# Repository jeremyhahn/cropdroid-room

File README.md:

# cropdroid-room

## Support

Please consider supporting this project for ongoing success and sustainability. I'm a passionate open source contributor making a professional living creating free, secure, scalable, robust, enterprise grade, distributed systems and cloud native solutions.

I'm also available for international consulting opportunities. Please let me know how I can assist you or your organization in achieving your desired security posture and technology goals.

https://github.com/sponsors/jeremyhahn

https://www.linkedin.com/in/jeremyhahn

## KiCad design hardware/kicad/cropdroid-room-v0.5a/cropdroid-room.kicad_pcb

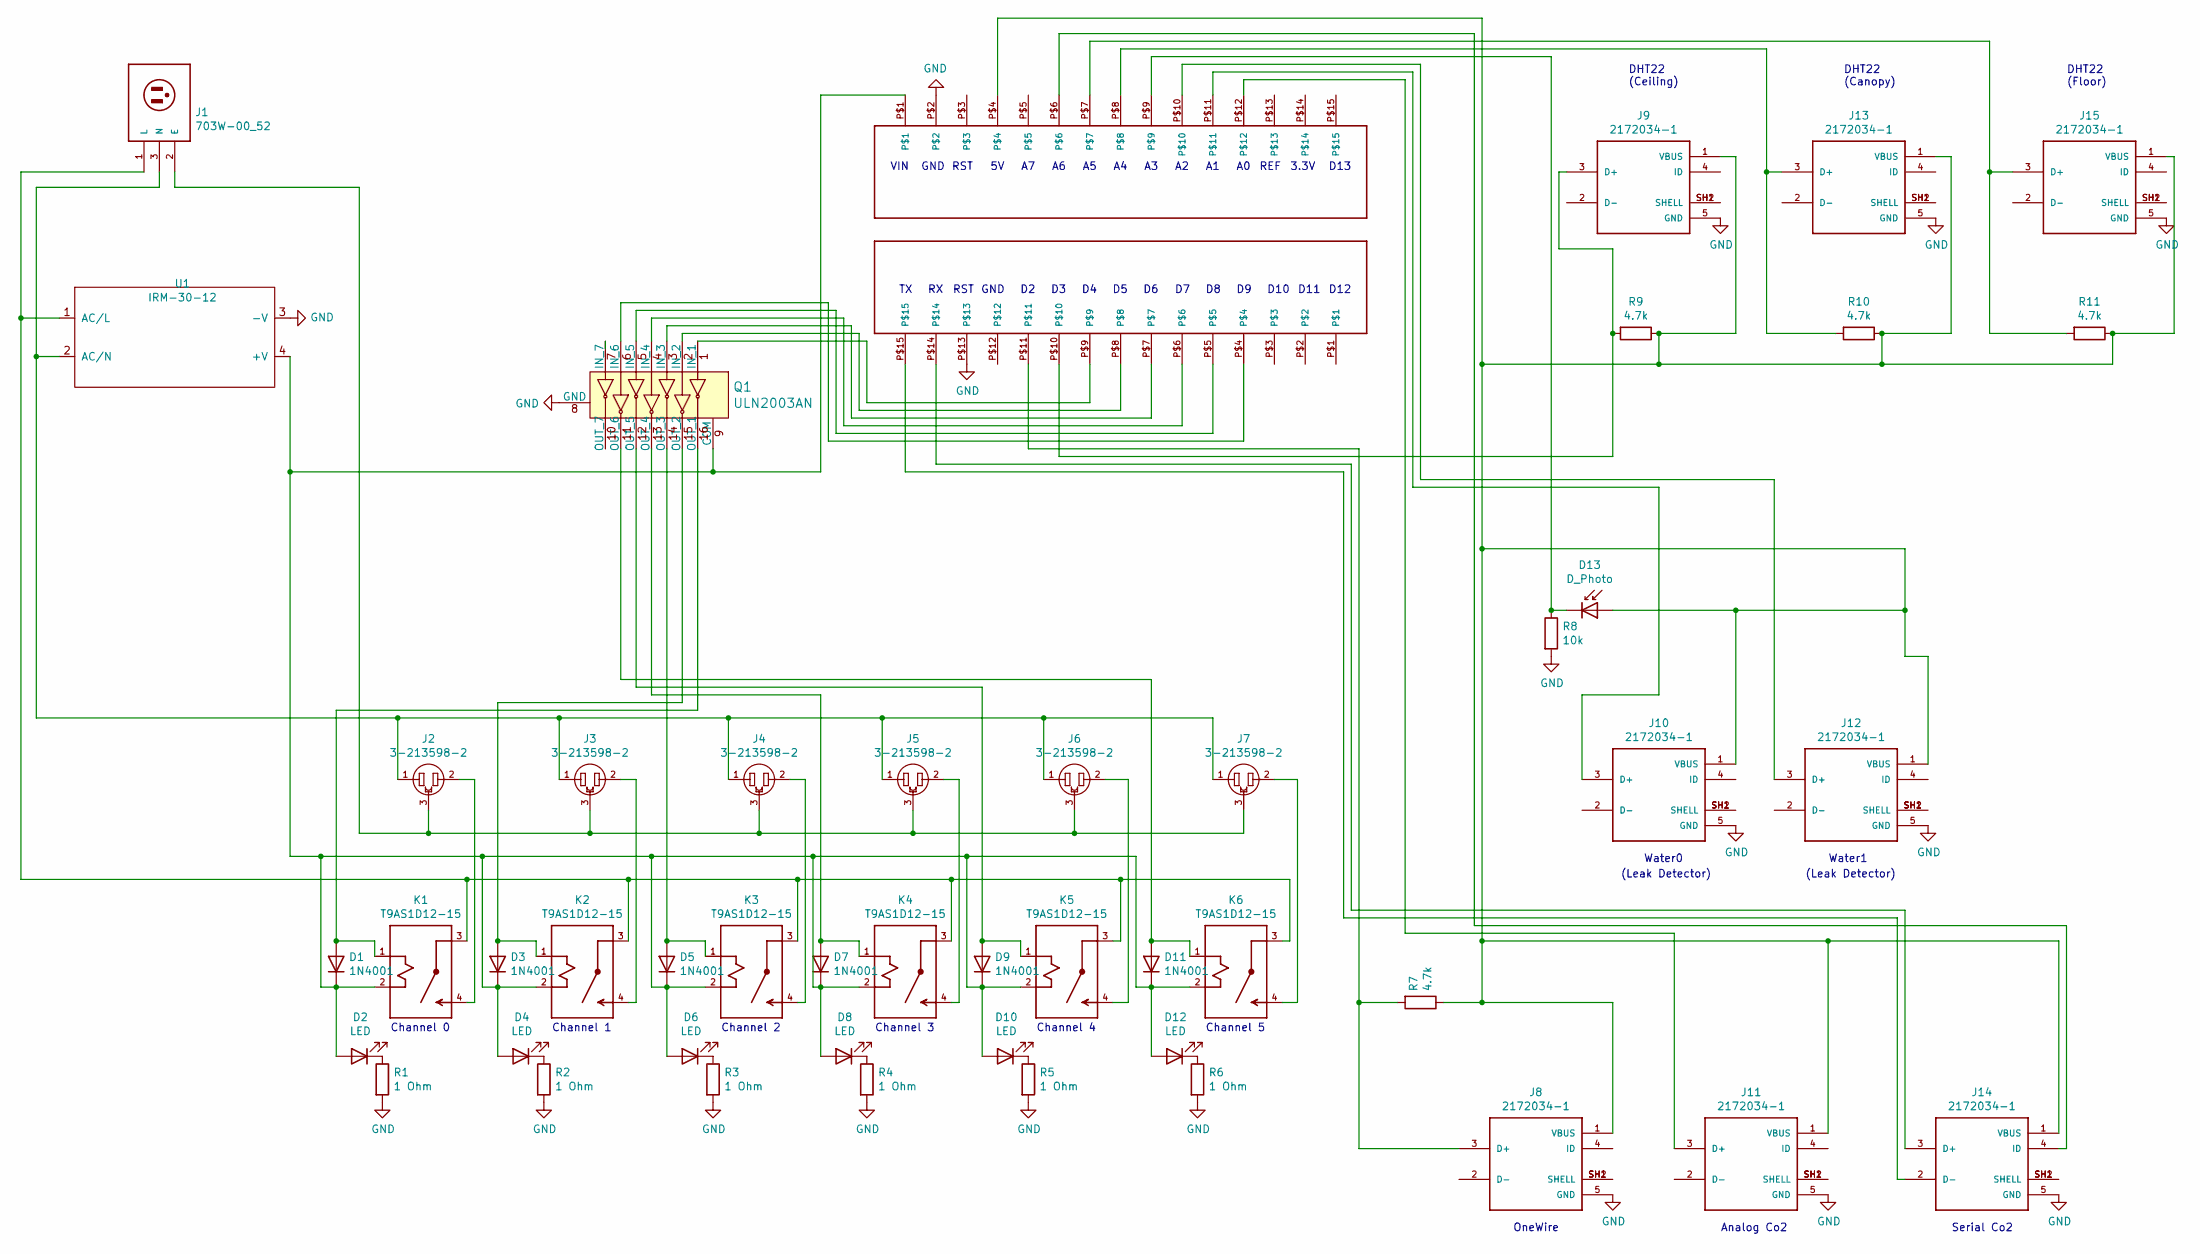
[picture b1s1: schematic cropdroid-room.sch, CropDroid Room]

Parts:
D1, D3, D5, D7, D9, D11: 1N4001; D_DO-41_SOD81_P10.16mm_Horizontal
D2, D4, D6, D8, D10, D12: LED; CAPPRD350W60D800H2000
D13: D_Photo; PHODET_PDV-P8103
J1: 703W-00_52; 52
J2, J3, J4, J5, J6, J7: 3-213598-2; TE_3-213598-2
J8, J9, J10, J11, J12, J13, J14, J15: 2172034-1; TE_2172034-1
K1, K2, K3, K4, K5, K6: T9AS1D12-15; RELAY_T9AS1D12-15
Q1: ULN2003AN; DIP-16_W7.62mm; MPN ULN2003AN; Digi-Key_PN 296-1979-5-ND
R1, R2, R3, R4, R5, R6: 1 Ohm; R_Axial_DIN0207_L6.3mm_D2.5mm_P10.16mm_Horizontal
R7, R9, R10, R11: 4.7k; R_Axial_DIN0207_L6.3mm_D2.5mm_P10.16mm_Horizontal
R8: 10k; R_Axial_DIN0207_L6.3mm_D2.5mm_P10.16mm_Horizontal
U1: IRM-30-12
U2, U3: PPTC151LFBN-RC

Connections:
GND: J8.5 (GND), J9.5 (GND), J10.5 (GND), J11.5 (GND), J12.5 (GND), J13.5 (GND), J14.5 (GND), J15.5 (GND), Q1.8 (GND), R1.2, R2.2, R3.2, R4.2, R5.2, R6.2, R8.2, U1.3 (-V), U2.P$2, U3.P$13
unnamed: D1.1 (K), D2.2 (A), D3.1 (K), D4.2 (A), D5.1 (K), D6.2 (A), D7.1 (K), D8.2 (A), D9.1 (K), D10.2 (A), D11.1 (K), D12.2 (A), K1.2 (A2), K2.2 (A2), K3.2 (A2), K4.2 (A2), K5.2 (A2), K6.2 (A2), Q1.9 (COM), U1.4 (+V), U2.P$1
unnamed: D1.2 (A), K1.1 (A1), Q1.16 (OUT_1)
unnamed: D2.1 (K), R1.1
unnamed: D3.2 (A), K2.1 (A1), Q1.15 (OUT_2)
unnamed: D4.1 (K), R2.1
unnamed: D5.2 (A), K3.1 (A1), Q1.14 (OUT_3)
unnamed: D6.1 (K), R3.1
unnamed: D7.2 (A), K4.1 (A1), Q1.13 (OUT_4)
unnamed: D8.1 (K), R4.1
unnamed: D9.2 (A), K5.1 (A1), Q1.12 (OUT_5)
unnamed: D10.1 (K), R5.1
unnamed: D11.2 (A), K6.1 (A1), Q1.11 (OUT_6)
unnamed: D12.1 (K), R6.1
unnamed: D13.1 (K), R8.1, U2.P$9
unnamed: D13.2 (A), J8.1 (VBUS), J9.1 (VBUS), J10.1 (VBUS), J11.1 (VBUS), J12.1 (VBUS), J13.1 (VBUS), J14.1 (VBUS), J15.1 (VBUS), R7.1, R9.1, R10.1, R11.1, U2.P$4
unnamed: J1.1 (L), K1.3 (C), K2.3 (C), K3.3 (C), K4.3 (C), K5.3 (C), K6.3 (C), U1.1 (AC/L)
unnamed: J1.2 (E), J2.3, J3.3, J4.3, J5.3, J6.3, J7.3
unnamed: J1.3 (N), J2.1, J3.1, J4.1, J5.1, J6.1, J7.1, U1.2 (AC/N)
unnamed: J2.2, K1.4 (NO)
unnamed: J3.2, K2.4 (NO)
unnamed: J4.2, K3.4 (NO)
unnamed: J5.2, K4.4 (NO)
unnamed: J6.2, K5.4 (NO)
unnamed: J7.2, K6.4 (NO)
unnamed: J8.3 (D+), R7.2, U3.P$11
unnamed: J8.SH1 (SHELL), J8.SH2 (SHELL)
unnamed: J9.3 (D+), R9.2, U3.P$10
unnamed: J9.SH1 (SHELL), J9.SH2 (SHELL)
unnamed: J10.3 (D+), U2.P$11
unnamed: J10.SH1 (SHELL), J10.SH2 (SHELL)
unnamed: J11.3 (D+), U2.P$12
unnamed: J11.SH1 (SHELL), J11.SH2 (SHELL)
unnamed: J12.3 (D+), U2.P$10
unnamed: J12.SH1 (SHELL), J12.SH2 (SHELL)
unnamed: J13.3 (D+), R10.2, U2.P$8
unnamed: J13.SH1 (SHELL), J13.SH2 (SHELL)
unnamed: J14.2 (D-), U3.P$15
unnamed: J14.3 (D+), U3.P$14
unnamed: J14.4 (ID), U2.P$6
unnamed: J14.SH1 (SHELL), J14.SH2 (SHELL)
unnamed: J15.3 (D+), R11.2, U2.P$7
unnamed: J15.SH1 (SHELL), J15.SH2 (SHELL)
unnamed: Q1.1 (IN_1), U3.P$9
unnamed: Q1.2 (IN_2), U3.P$8
unnamed: Q1.3 (IN_3), U3.P$7
unnamed: Q1.4 (IN_4), U3.P$6
unnamed: Q1.5 (IN_5), U3.P$5
unnamed: Q1.6 (IN_6), U3.P$4

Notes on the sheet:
Water0
Water1
(Leak Detector)
Channel 1
Channel 2
Channel 3
Channel 4
Channel 0
DHT22 (Ceiling)
DHT22 (Canopy)
DHT22 (Floor)
Channel 5
D12
D11
D10
D13
3.3V
REF
RST
GND
VIN
Analog Co2
OneWire
Serial Co2

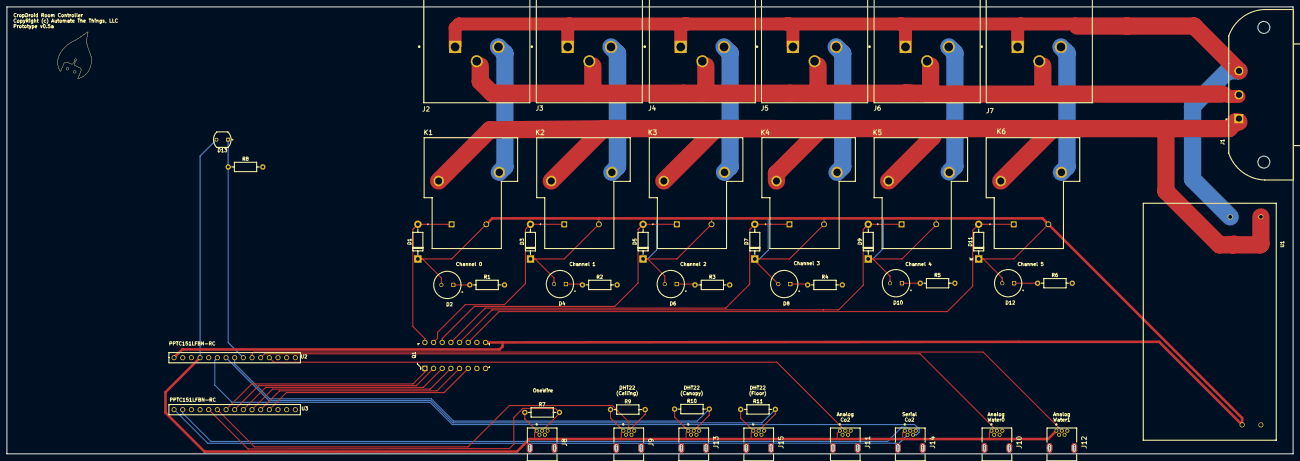
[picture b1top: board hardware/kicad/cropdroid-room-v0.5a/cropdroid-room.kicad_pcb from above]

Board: 2 copper layers, 377.2 x 131.1 mm, 49 parts (0 on the bottom side), 49 nets.

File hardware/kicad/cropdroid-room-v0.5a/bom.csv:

Reference, Quantity, Value, Footprint, Datasheet, Category, DK_Datasheet_Link, DK_Detail_Page, Description, Digi-Key_PN, Family, MPN, Manufacturer, Status, Field4, Field5, Field6
D13 ,1,"D_Photo","libraries:PHODET_PDV-P8103","~"
D3 D5 D7 D9 D1 D11 ,6,"1N4001","Diode_THT:D_DO-41_SOD81_P10.16mm_Horizontal","http://www.vishay.com/docs/88503/1n4001.pdf"
D4 D6 D8 D10 D2 D12 ,6,"LED","libraries:CAPPRD350W60D800H2000","~"
J1 ,1,"703W-00_52","703W-00_52:52","Qualtek","","","","","","","","","","B","Manufacturer Recommendations",""
J2 J3 J4 J5 J6 J7 ,6,"3-213598-2","3-213598-2:TE_3-213598-2","https://www.te.com/usa-en/product-3-213598-2.html?te_bu=Cor&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","","","","","","","","","","Compliant","3-213598-2","Convenience Outlet"
J9 J13 J15 J10 J12 J8 J11 J14 ,8,"2172034-1","TE_2172034-1","Compliant","","","","","","","","","","2172034-1","https://www.te.com/usa-en/product-2172034-1.html?te_bu=Cor&t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",""
K2 K3 K4 K5 K1 K6 ,6,"T9AS1D12-15","T9AS1D12-15:RELAY_T9AS1D12-15","https://www.te.com/usa-en/product-1-1393210-4.html?te_bu=Cor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","","","","","","","","","","1-1393210-4","",""
Q1 ,1,"ULN2003AN","digikey-footprints:DIP-16_W7.62mm","http://www.ti.com/general/docs/suppproductinfo.tsp?distId=10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","Discrete Semiconductor Products","http://www.ti.com/general/docs/suppproductinfo.tsp?distId=10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","/product-detail/en/texas-instruments/ULN2003AN/296-1979-5-ND/277624","IC PWR RELAY 7NPN 1:1 16DIP","296-1979-5-ND","Transistors - Bipolar (BJT) - Arrays","ULN2003AN","Texas Instruments","Active","","",""
R2 R3 R4 R5 R1 R6 ,6,"1 Ohm","Resistor_THT:R_Axial_DIN0207_L6.3mm_D2.5mm_P10.16mm_Horizontal","~"
R8 ,1,"10k","Resistor_THT:R_Axial_DIN0207_L6.3mm_D2.5mm_P10.16mm_Horizontal","~"
R9 R10 R11 R7 ,4,"4.7k","Resistor_THT:R_Axial_DIN0207_L6.3mm_D2.5mm_P10.16mm_Horizontal","~"
U1 ,1,"IRM-30-12","IRM-30-12:IRM-30-12",""
U3 U2 ,2,"PPTC151LFBN-RC","PPTC151LFBN-RC:PPTC151LFBN-RC",""

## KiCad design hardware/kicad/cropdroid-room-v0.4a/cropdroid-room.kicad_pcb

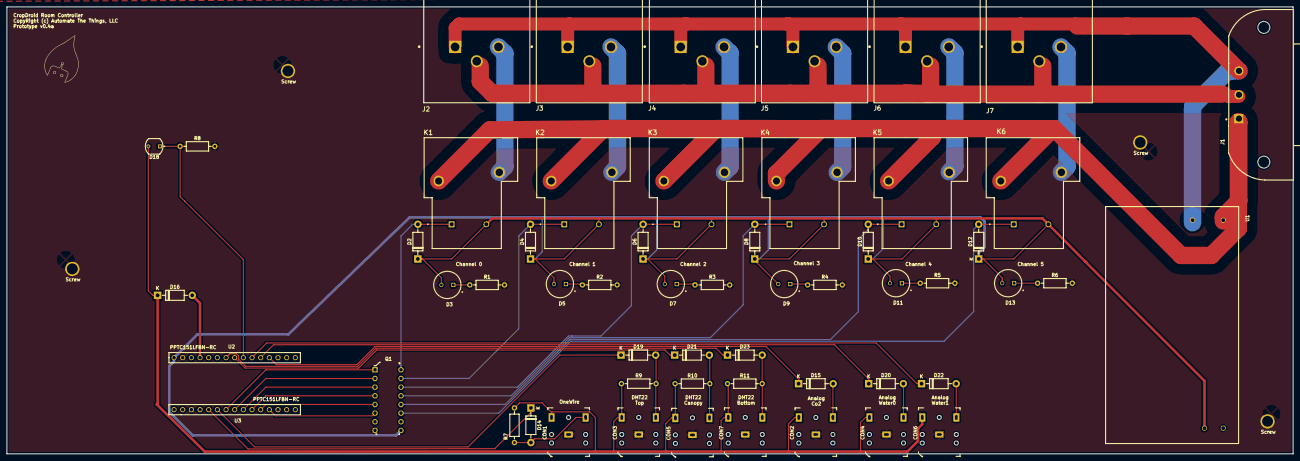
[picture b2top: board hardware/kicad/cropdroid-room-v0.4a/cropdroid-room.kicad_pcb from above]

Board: 2 copper layers, 377.2 x 131.1 mm, 60 parts (0 on the bottom side), 46 nets.

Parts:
CON1, CON2, CON3, CON4, CON5, CON6, CON7: SJ1-3523N; Headphone_Jack_3.5mm_SJ1-3523N
D2, D4, D6, D8, D10, D12, D14, D15, D16, D19, D20, D21, D22, D23: 1N4001; D_DO-41_SOD81_P10.16mm_Horizontal
D3, D5, D7, D9, D11, D13: LED; CAPPRD350W60D800H2000
D18: D_Photo; PHODET_PDV-P8103
J1: 703W-00_52; 52
J2, J3, J4, J5, J6, J7: 3-213598-2; TE_3-213598-2
K1, K2, K3, K4, K5, K6: T9AS1D12-15; RELAY_T9AS1D12-15
Q1: ULN2003AN; DIP-16_W7.62mm
R1, R2, R3, R4, R5, R6: 1 Ohm; R_Axial_DIN0207_L6.3mm_D2.5mm_P10.16mm_Horizontal
R7, R9, R10, R11: 4.7k; R_Axial_DIN0207_L6.3mm_D2.5mm_P10.16mm_Horizontal
R8: 10k; R_Axial_DIN0207_L6.3mm_D2.5mm_P10.16mm_Horizontal
Screw: Drill; Drill_Hole
Screw#2, Screw#3, Screw#4: Drill; Drill_Hole
U1: IRM-30-12
U2, U3: PPTC151LFBN-RC

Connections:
GND: CON1.1, CON2.1, CON3.1, CON4.1, CON5.1, CON6.1, CON7.1, Q1.8, R1.2, R2.2, R3.2, R4.2, R5.2, R6.2, R8.2, U1.3, U2.P$2, U3.P$13
unnamed: CON1.2, D14.2, R7.2
unnamed: CON1.3, CON2.3, CON3.3, CON4.3, CON5.3, CON6.3, CON7.3, D16.1, D18.2, R7.1, R9.1, R10.1, R11.1
unnamed: CON2.2, D15.2
unnamed: CON3.2, D19.2, R9.2
unnamed: CON4.2, D20.2
unnamed: CON5.2, D21.2, R10.2
unnamed: CON6.2, D22.2
unnamed: CON7.2, D23.2, R11.2
unnamed: D2.2, K1.1, Q1.16
unnamed: D3.1, R1.1
unnamed: D4.2, K2.1, Q1.15
unnamed: D5.1, R2.1
unnamed: D6.2, K3.1, Q1.14
unnamed: D7.1, R3.1
unnamed: D8.2, K4.1, Q1.13
unnamed: D9.1, R4.1
unnamed: D2.1, D3.2, D4.1, D5.2, D6.1, D7.2, D8.1, D9.2, D10.1, D11.2, D12.1, D13.2, K1.2, K2.2, K3.2, K4.2, K5.2, K6.2, Q1.9, U1.4, U2.P$1
unnamed: D10.2, K5.1, Q1.12
unnamed: D11.1, R5.1
unnamed: D12.2, K6.1, Q1.11
unnamed: D13.1, R6.1
unnamed: D14.1, U3.P$11
unnamed: D15.1, U2.P$12
unnamed: D16.2, U2.P$4
unnamed: D18.1, R8.1, U2.P$9
unnamed: D19.1, U3.P$10
unnamed: D20.1, U2.P$11
unnamed: D21.1, U2.P$8
unnamed: D22.1, U2.P$10
unnamed: D23.1, U2.P$7
unnamed: J1.1, K1.3, K2.3, K3.3, K4.3, K5.3, K6.3, U1.1
unnamed: J1.2, J2.3, J3.3, J4.3, J5.3, J6.3, J7.3
unnamed: J1.3, J2.1, J3.1, J4.1, J5.1, J6.1, J7.1, U1.2
unnamed: J2.2, K1.4
unnamed: J3.2, K2.4
unnamed: J4.2, K3.4
unnamed: J5.2, K4.4
unnamed: J6.2, K5.4
unnamed: J7.2, K6.4
unnamed: Q1.1, U3.P$9
unnamed: Q1.2, U3.P$8
unnamed: Q1.3, U3.P$7
unnamed: Q1.4, U3.P$6
unnamed: Q1.5, U3.P$5
unnamed: Q1.6, U3.P$4

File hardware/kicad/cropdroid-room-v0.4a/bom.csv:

Reference, Quantity, Value, Footprint, Datasheet, Category, DK_Datasheet_Link, DK_Detail_Page, Description, Digi-Key_PN, Family, MPN, Manufacturer, Status, Field4, Field5, Field6
CON6 CON3 CON5 CON7 CON4 CON2 CON1 ,7,"SJ1-3523N","digikey-footprints:Headphone_Jack_3.5mm_SJ1-3523N","https://www.cui.com/product/resource/digikeypdf/sj1-352xn_se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","Connectors, Interconnects","https://www.cui.com/product/resource/digikeypdf/sj1-352xn_se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","/product-detail/en/cui-inc/SJ1-3523N/CP1-3523N-ND/738689","CONN JACK STEREO 3.5MM R/A","CP1-3523N-ND","Barrel - Audio Connectors","SJ1-3523N","CUI Inc.","Active","","",""
D1 ,1,"1N5400","Diode_THT:D_DO-201AD_P15.24mm_Horizontal","http://www.vishay.com/docs/88516/1n5400.pdf"
D18 ,1,"D_Photo","libraries:PHODET_PDV-P8103","~"
D4 D6 D8 D10 D2 D12 D23 D21 D20 D22 D19 D14 D15 D16 ,14,"1N4001","Diode_THT:D_DO-41_SOD81_P10.16mm_Horizontal","http://www.vishay.com/docs/88503/1n4001.pdf"
D5 D7 D9 D11 D3 D13 ,6,"LED","libraries:CAPPRD350W60D800H2000","~"
J1 ,1,"703W-00_52","703W-00_52:52","Qualtek","","","","","","","","","","B","Manufacturer Recommendations",""
J2 J3 J4 J5 J6 J7 ,6,"3-213598-2","3-213598-2:TE_3-213598-2","https://www.te.com/usa-en/product-3-213598-2.html?te_bu=Cor&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","","","","","","","","","","Compliant","3-213598-2","Convenience Outlet"
K2 K3 K4 K5 K1 K6 ,6,"T9AS1D12-15","T9AS1D12-15:RELAY_T9AS1D12-15","https://www.te.com/usa-en/product-1-1393210-4.html?te_bu=Cor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","","","","","","","","","","1-1393210-4","",""
Q1 ,1,"ULN2003AN","digikey-footprints:DIP-16_W7.62mm","http://www.ti.com/general/docs/suppproductinfo.tsp?distId=10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","Discrete Semiconductor Products","http://www.ti.com/general/docs/suppproductinfo.tsp?distId=10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","/product-detail/en/texas-instruments/ULN2003AN/296-1979-5-ND/277624","IC PWR RELAY 7NPN 1:1 16DIP","296-1979-5-ND","Transistors - Bipolar (BJT) - Arrays","ULN2003AN","Texas Instruments","Active","","",""
R2 R3 R4 R5 R1 R6 ,6,"1 Ohm","Resistor_THT:R_Axial_DIN0207_L6.3mm_D2.5mm_P10.16mm_Horizontal","~"
R8 ,1,"10k","Resistor_THT:R_Axial_DIN0207_L6.3mm_D2.5mm_P10.16mm_Horizontal","~"
R9 R10 R11 R7 ,4,"4.7k","Resistor_THT:R_Axial_DIN0207_L6.3mm_D2.5mm_P10.16mm_Horizontal","~"
U1 ,1,"IRM-30-12","IRM-30-12:IRM-30-12",""
U3 U2 ,2,"PPTC151LFBN-RC","PPTC151LFBN-RC:PPTC151LFBN-RC",""

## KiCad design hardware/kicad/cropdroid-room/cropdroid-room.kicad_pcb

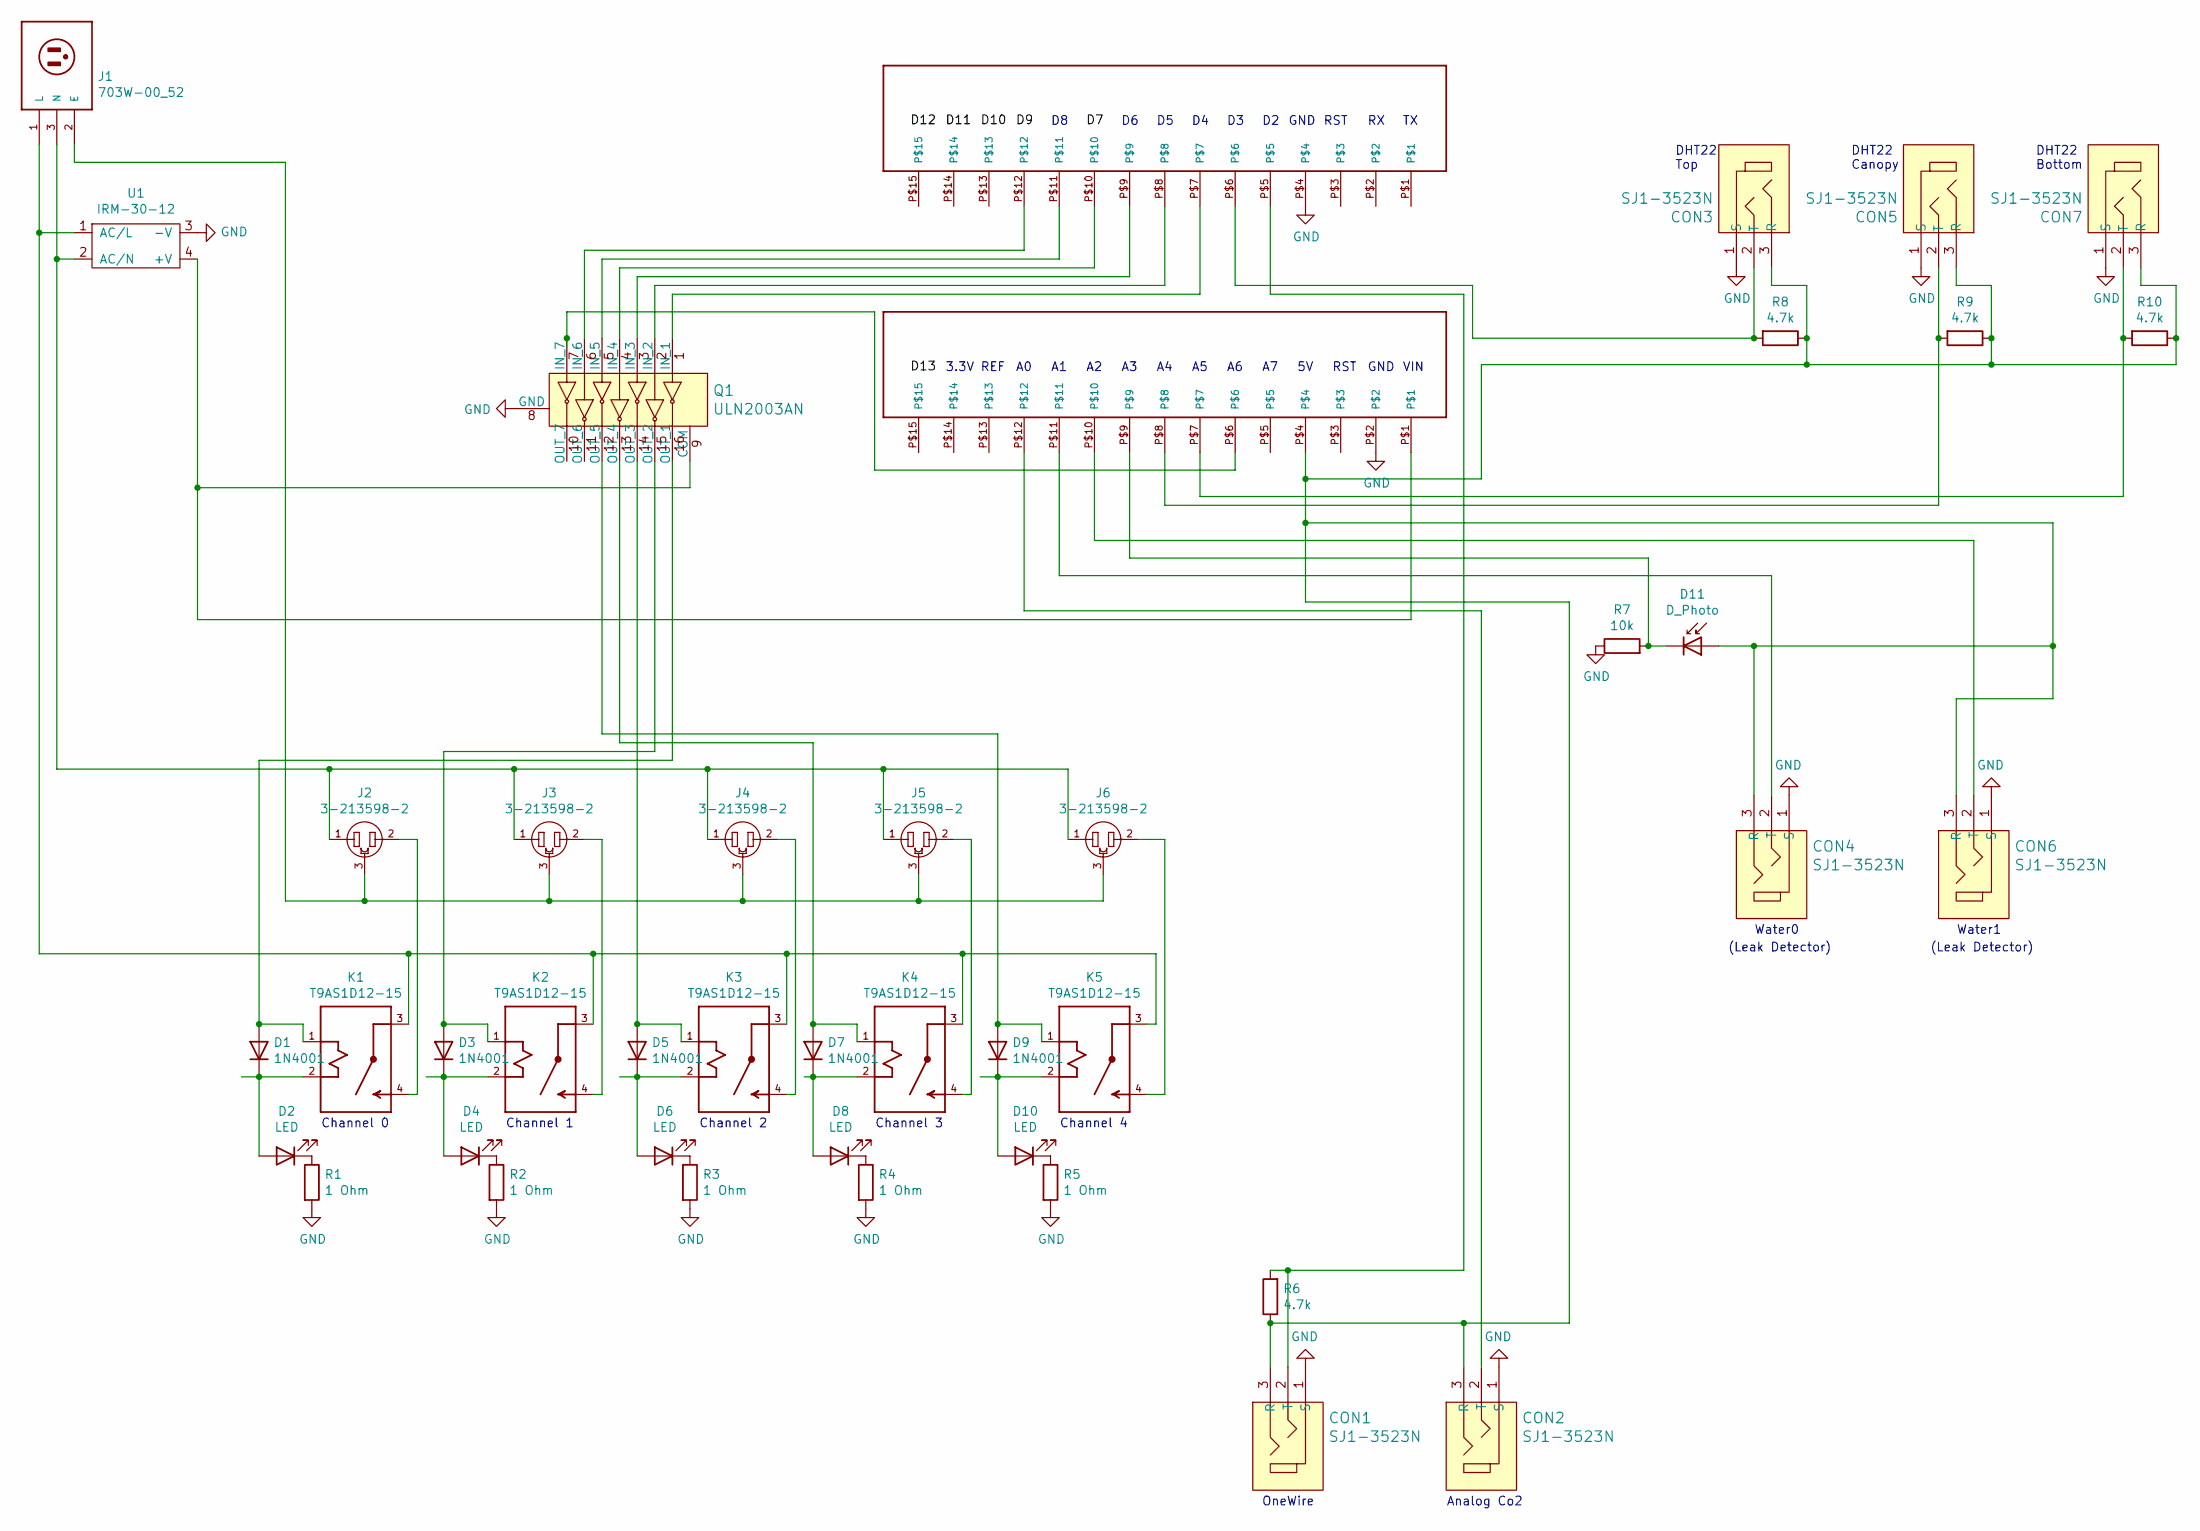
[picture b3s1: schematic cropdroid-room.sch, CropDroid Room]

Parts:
CON1, CON2, CON3, CON4, CON5, CON6, CON7: SJ1-3523N; Headphone_Jack_3.5mm_SJ1-3523N; MPN SJ1-3523N; Digi-Key_PN CP1-3523N-ND
D1, D3, D5, D7, D9: 1N4001; D_DO-41_SOD81_P10.16mm_Horizontal
D2, D4, D6, D8, D10: LED; CAPPRD350W60D800H2000
D11: D_Photo; PHODET_PDV-P8103
J1: 703W-00_52; 52
J2, J3, J4, J5, J6: 3-213598-2; TE_3-213598-2
K1, K2, K3, K4, K5: T9AS1D12-15; RELAY_T9AS1D12-15
Q1: ULN2003AN; DIP-16_W7.62mm; MPN ULN2003AN; Digi-Key_PN 296-1979-5-ND
R1, R2, R3, R4, R5: 1 Ohm; R_Axial_DIN0207_L6.3mm_D2.5mm_P10.16mm_Horizontal
R6, R8, R9, R10: 4.7k; R_Axial_DIN0207_L6.3mm_D2.5mm_P10.16mm_Horizontal
R7: 10k; R_Axial_DIN0207_L6.3mm_D2.5mm_P10.16mm_Horizontal
U1: IRM-30-12
U2, U3: PPTC151LFBN-RC

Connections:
GND: CON1.1 (S), CON2.1 (S), CON3.1 (S), CON4.1 (S), CON5.1 (S), CON6.1 (S), CON7.1 (S), Q1.8 (GND), R1.2, R2.2, R3.2, R4.2, R5.2, R7.1, U1.3 (-V), U2.P$4, U3.P$2
unnamed: CON1.2 (T), R6.2, U2.P$5
unnamed: CON1.3 (R), CON2.3 (R), CON3.3 (R), CON4.3 (R), CON5.3 (R), CON6.3 (R), CON7.3 (R), D11.2 (A), R6.1, R8.1, R9.1, R10.1, U3.P$4
unnamed: CON2.2 (T), U3.P$12
unnamed: CON3.2 (T), R8.2, U2.P$6
unnamed: CON4.2 (T), U3.P$11
unnamed: CON5.2 (T), R9.2, U3.P$8
unnamed: CON6.2 (T), U3.P$10
unnamed: CON7.2 (T), R10.2, U3.P$7
unnamed: D1.1 (K), D2.2 (A), K1.2 (A2)
unnamed: D1.2 (A), K1.1 (A1), Q1.16 (OUT_1)
unnamed: D2.1 (K), R1.1
unnamed: D3.1 (K), D4.2 (A), K2.2 (A2)
unnamed: D3.2 (A), K2.1 (A1), Q1.15 (OUT_2)
unnamed: D4.1 (K), R2.1
unnamed: D5.1 (K), D6.2 (A), K3.2 (A2)
unnamed: D5.2 (A), K3.1 (A1), Q1.14 (OUT_3)
unnamed: D6.1 (K), R3.1
unnamed: D7.1 (K), D8.2 (A), K4.2 (A2)
unnamed: D7.2 (A), K4.1 (A1), Q1.13 (OUT_4)
unnamed: D8.1 (K), R4.1
unnamed: D9.2 (A), K5.1 (A1), Q1.12 (OUT_5)
unnamed: D10.1 (K), R5.1
unnamed: D9.1 (K), D10.2 (A), K5.2 (A2)
unnamed: D11.1 (K), R7.2, U3.P$9
unnamed: J1.1 (L), K1.3 (C), K2.3 (C), K3.3 (C), K4.3 (C), K5.3 (C), U1.1 (AC/L)
unnamed: J1.2 (E), J2.3, J3.3, J4.3, J5.3, J6.3
unnamed: J1.3 (N), J2.1, J3.1, J4.1, J5.1, J6.1, U1.2 (AC/N)
unnamed: J2.2, K1.4 (NO)
unnamed: J3.2, K2.4 (NO)
unnamed: J4.2, K3.4 (NO)
unnamed: J5.2, K4.4 (NO)
unnamed: J6.2, K5.4 (NO)
unnamed: Q1.1 (IN_1), U2.P$7
unnamed: Q1.2 (IN_2), U2.P$8
unnamed: Q1.3 (IN_3), U2.P$9
unnamed: Q1.4 (IN_4), U2.P$10
unnamed: Q1.5 (IN_5), U2.P$11
unnamed: Q1.6 (IN_6), U2.P$12
unnamed: Q1.7 (IN_7), U3.P$6
unnamed: Q1.9 (COM), U1.4 (+V), U3.P$1

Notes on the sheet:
GND
RST
3.3V
REF
VIN
Water0
Water1
(Leak Detector)
Channel 1
Channel 2
Channel 3
Channel 4
Channel 0
DHT22 Top
DHT22 Canopy
DHT22 Bottom
Analog Co2
OneWire

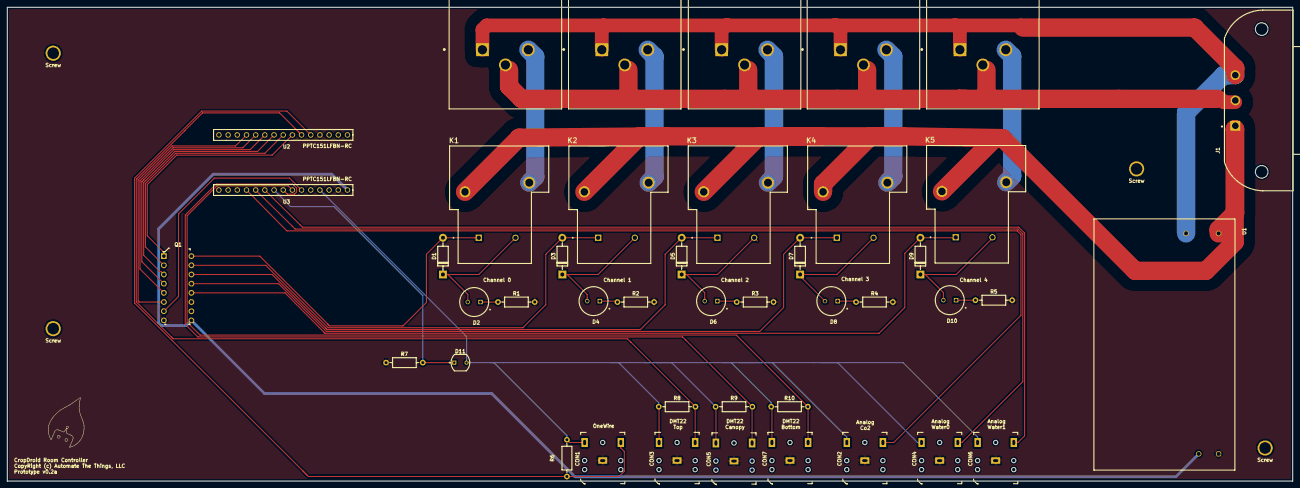
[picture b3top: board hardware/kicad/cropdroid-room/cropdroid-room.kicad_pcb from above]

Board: 2 copper layers, 355.6 x 131.1 mm, 47 parts (0 on the bottom side), 41 nets.

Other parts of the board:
Screw: Drill; Drill_Hole
Screw#2, Screw#3, Screw#4: Drill; Drill_Hole

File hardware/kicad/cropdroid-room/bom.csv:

Reference, Quantity, Value, Footprint, Datasheet, Category, DK_Datasheet_Link, DK_Detail_Page, Description, Digi-Key_PN, Family, MPN, Manufacturer, Status, Field4, Field5, Field6
CON6 CON3 CON5 CON7 CON4 CON2 CON1 ,7,"SJ1-3523N","digikey-footprints:Headphone_Jack_3.5mm_SJ1-3523N","https://www.cui.com/product/resource/digikeypdf/sj1-352xn_se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","Connectors, Interconnects","https://www.cui.com/product/resource/digikeypdf/sj1-352xn_se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","/product-detail/en/cui-inc/SJ1-3523N/CP1-3523N-ND/738689","CONN JACK STEREO 3.5MM R/A","CP1-3523N-ND","Barrel - Audio Connectors","SJ1-3523N","CUI Inc.","Active","","",""
D11 ,1,"D_Photo","libraries:PHODET_PDV-P8103","~"
D3 D5 D7 D9 D1 ,5,"1N4001","Diode_THT:D_DO-41_SOD81_P10.16mm_Horizontal","http://www.vishay.com/docs/88503/1n4001.pdf"
D4 D6 D8 D10 D2 ,5,"LED","libraries:CAPPRD350W60D800H2000","~"
J1 ,1,"703W-00_52","703W-00_52:52","Qualtek","","","","","","","","","","B","Manufacturer Recommendations",""
J2 J3 J4 J5 J6 ,5,"3-213598-2","3-213598-2:TE_3-213598-2","https://www.te.com/usa-en/product-3-213598-2.html?te_bu=Cor&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","","","","","","","","","","Compliant","3-213598-2","Convenience Outlet"
K2 K3 K4 K5 K1 ,5,"T9AS1D12-15","T9AS1D12-15:RELAY_T9AS1D12-15","https://www.te.com/usa-en/product-1-1393210-4.html?te_bu=Cor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","","","","","","","","","","1-1393210-4","",""
Q1 ,1,"ULN2003AN","digikey-footprints:DIP-16_W7.62mm","http://www.ti.com/general/docs/suppproductinfo.tsp?distId=10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","Discrete Semiconductor Products","http://www.ti.com/general/docs/suppproductinfo.tsp?distId=10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","/product-detail/en/texas-instruments/ULN2003AN/296-1979-5-ND/277624","IC PWR RELAY 7NPN 1:1 16DIP","296-1979-5-ND","Transistors - Bipolar (BJT) - Arrays","ULN2003AN","Texas Instruments","Active","","",""
R2 R3 R4 R5 R1 ,5,"1 Ohm","Resistor_THT:R_Axial_DIN0207_L6.3mm_D2.5mm_P10.16mm_Horizontal","~"
R7 ,1,"10k","Resistor_THT:R_Axial_DIN0207_L6.3mm_D2.5mm_P10.16mm_Horizontal","~"
R8 R9 R10 R6 ,4,"4.7k","Resistor_THT:R_Axial_DIN0207_L6.3mm_D2.5mm_P10.16mm_Horizontal","~"
U1 ,1,"IRM-30-12","IRM-30-12:IRM-30-12",""
U2 U3 ,2,"PPTC151LFBN-RC","PPTC151LFBN-RC:PPTC151LFBN-RC",""

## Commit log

2019-02-10 ignore build dir
2019-02-10 remove build dir
2019-02-10 add co2 and water level sensors
2019-02-12 Add VPD calculation
2019-02-15 remove arest. initial deployment
2019-02-27 shorten rest variable names
2019-03-06 add photo sensor and dehu pin
2019-03-10 move strings to progmem. add dehu and fan endpoints. only enable/print to serial if DEBUG enabled
2019-03-10 optimize memory. expose remaining analog and digital pins as switches
2019-03-10 revert to default mac address
2019-03-13 fix memory leak. add eeprom library
2019-03-27 eeprom mac/ip. add /reset endpoint
2019-04-03 add content-type json header
2019-04-03 fix json formatting bug
2019-04-05 output json channel ids instead of pin numbers
2019-04-05 fix invalid channel when channel is 0 bug
2019-04-05 change name to cropdroid-room
2019-04-29 cleanup channel array
2019-05-08 add 2nd and 3rd DHT sensors. refactor switch endpoint to return channel and pin
2019-06-12 fix example curl eeprom default ip. optimize switch resource
2020-02-04 add kicad project
2020-02-05 finalize prototype v0.1a
2020-02-10 upgrade hardware to v0.2a (120v)
2020-02-10 final kicad v0.2a
2020-02-14 iterate on kicad room v0.3a
2020-02-14 fix kicad v0.3a co2 circuit missing diode and connection to microcontroller
2020-02-14 more v0.3a fixes
2020-02-14 add latest bom
2020-02-21 room v0.4a
2020-03-02 add v0.5a hardware
2020-03-11 add /sys endpoint
2020-04-13 return metrics as array. refactor /timer, /reboot and /reset endpoints
2020-04-13 return metrics as array instead of array of objects
2021-07-27 fix memory leak and channel size bug. create test suite. change DHT pins 2 and 3 to A6 and A7
2021-08-15 move dht to a4 and a5
2021-09-18 bump hardware room-v0.1b and firmware v1.0.0b
2024-01-16 Add Makefile firmware download target. Add hardware image to README
2024-01-16 Add hardware flow image
2024-07-07 Add Fusion 360 images and source files
2024-07-07 update readme with links to Fusion 360 images

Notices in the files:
hardware/kicad/cropdroid-room-v0.4a/cropdroid-room.kicad_pcb:
License: Proprietary
CopyRight (c) Automate The Things, LLC
